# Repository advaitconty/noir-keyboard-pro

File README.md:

# Noir Keyboard Pro
A keyboard designed around the iPad Pro 11inch, mainly for use on the side

## Features
- Choc Red Pro switches that are hotswappable to your heart's content
- A simple design with extra pins if anything extra is required for a Pico
- A stabilizer-less design allowing for just nice uses

## BOM
*Prices in USD*

|Item                                                                                        |Quantity|Full Price|Remarks                  |Link                                                                                                                                                                                                                                                                                                                                                                                                                                                                                                                                                                                                                                                                                                                                                                                                                                                                                                                                                                                                                                                                                                                  |
|--------------------------------------------------------------------------------------------|--------|----------|-------------------------|----------------------------------------------------------------------------------------------------------------------------------------------------------------------------------------------------------------------------------------------------------------------------------------------------------------------------------------------------------------------------------------------------------------------------------------------------------------------------------------------------------------------------------------------------------------------------------------------------------------------------------------------------------------------------------------------------------------------------------------------------------------------------------------------------------------------------------------------------------------------------------------------------------------------------------------------------------------------------------------------------------------------------------------------------------------------------------------------------------------------|
|EVA foam                                                                                    |1       |$1.29     |Black variant 3mm 30x50  |https://www.lazada.sg/products/eva-foam-board-production-1-10mm-thick-foam-board-i2849696182-s19642596230.html?                                                                                                                                                                                                                                                                                                                                                                                                                                                                                                                                                                                                                                                                                                                                                                                                                                                                                                                                                                                                       |
|Rasperry Pi Pico H                                                                          |1       |$15.52    |                         |https://www.lazada.sg/products/original-raspberry-pi-pico-2-pico-with-wireless-wifi-development-boardpico-or-pico-h-with-pin-header-support-mciropythonc-i3197404377-s21712146500.html?                                                                                                                                                                                                                                                                                                                                                                                                                                                                                                                                                                                                                                                                                                                                                                                                                                                                                                                               |
|Micro-USB to USB-C cable                                                                    |1       |$3.87     |                         |https://www.lazada.sg/products/pdp-i1856449135-s9890909408.html?c=&channelLpJumpArgs=&clickTrackInfo=query%253Amicro%252Busb%252Bto%252Btype%252Bc%253Bnid%253A1856449135%253Bsrc%253ALazadaMainSrp%253Brn%253A82dbcd556e292181194f71b02f7c3592%253Bregion%253Asg%253Bsku%253A1856449135_SGAMZ%253Bprice%253A4.99%253Bclient%253Adesktop%253Bsupplier_id%253A1000061401%253Bbiz_source%253Ah5_internal%253Bslot%253A15%253Butlog_bucket_id%253A470687%253Basc_category_id%253A9537%253Bitem_id%253A1856449135%253Bsku_id%253A9890909408%253Bshop_id%253A152117%253BtemplateInfo%253A-1_A3_C%25231103_L%2523107878_E%2523&freeshipping=1&fs_ab=2&fuse_fs=&lang=en&location=China&price=4.99&priceCompare=skuId%3A9890909408%3Bsource%3Alazada-search-voucher%3Bsn%3A82dbcd556e292181194f71b02f7c3592%3BoriginPrice%3A499%3BdisplayPrice%3A499%3BsinglePromotionId%3A-1%3BsingleToolCode%3AmockedSalePrice%3BvoucherPricePlugin%3A0%3Btimestamp%3A1754101450229&ratingscore=4.95945945945946&request_id=82dbcd556e292181194f71b02f7c3592&review=308&sale=896&search=1&source=search&spm=a2o42.searchlist.list.15&stock=1|
|Kailh Choc Red Pro Switches (v1)                                                            |100     |$41.15    |x90 piece                |https://www.lazada.sg/products/kailh-low-profile-choc-switch-1350-rgb-for-keyboard-crystal-red-pro-pale-blue-pink-robin-silver-brown-white-yellow-orange-i3235755317-s21882496922.html?                                                                                                                                                                                                                                                                                                                                                                                                                                                                                                                                                                                                                                                                                                                                                                                                                                                                                                                               |
|Schotky Diodes                                                                              |100     |$4.58     |x100 piece               |https://www.lazada.sg/products/1n4148-do-35-small-signal-fast-switching-diode-i2668535659-s17380791247.html?                                                                                                                                                                                                                                                                                                                                                                                                                                                                                                                                                                                                                                                                                                                                                                                                                                                                                                                                                                                                          |
|Kailh Choc Hotswap Socket                                                                   |100     |$13.97    |x90 piece                |https://www.lazada.sg/products/kailh-hot-swap-plug-socket-for-kailh-low-profile-switch-choc-1350-i3216869960-s21821088673.html?                                                                                                                                                                                                                                                                                                                                                                                                                                                                                                                                                                                                                                                                                                                                                                                                                                                                                                                                                                                       |
|Noir Keyboard Pro PCB from JLCPCB                                                           |5       |$15.70    |Purchased                |NA                                                                                                                                                                                                                                                                                                                                                                                                                                                                                                                                                                                                                                                                                                                                                                                                                                                                                                                                                                                                                                                                                                                    |
|128x32 OLED Screen                                                                          |1       |$0.64     |White variant            |https://www.lazada.sg/products/pdp-i3161600227-s21505742950.html?c=&channelLpJumpArgs=&clickTrackInfo=query%253A128x32%252Boled%253Bnid%253A3161600227%253Bsrc%253ALazadaMainSrp%253Brn%253A38595f117eee84b7634c277fce23234a%253Bregion%253Asg%253Bsku%253A3161600227_SGAMZ%253Bprice%253A0.83%253Bclient%253Adesktop%253Bsupplier_id%253A1143054051%253Bbiz_source%253Ah5_internal%253Bslot%253A2%253Butlog_bucket_id%253A470687%253Basc_category_id%253A10000489%253Bitem_id%253A3161600227%253Bsku_id%253A21505742950%253Bshop_id%253A1260616%253BtemplateInfo%253A-1_A3_C%25231103_L%2523107878_E%2523&freeshipping=1&fs_ab=2&fuse_fs=&lang=en&location=China&price=0.83&priceCompare=skuId%3A21505742950%3Bsource%3Alazada-search-voucher%3Bsn%3A38595f117eee84b7634c277fce23234a%3BoriginPrice%3A83%3BdisplayPrice%3A83%3BsinglePromotionId%3A-1%3BsingleToolCode%3AmockedSalePrice%3BvoucherPricePlugin%3A0%3Btimestamp%3A1754102022697&ratingscore=5.0&request_id=38595f117eee84b7634c277fce23234a&review=1&sale=12&search=1&source=search&spm=a2o42.searchlist.list.2&stock=1                                |
|Shipping label                                                                              |1       |$2.87     |For 3D printed parts     |https://www.singpost.com/send-receive/sending-within-singapore/postage-paid-packaging/smartpac                                                                                                                                                                                                                                                                                                                                                                                                                                                                                                                                                                                                                                                                                                                                                                                                                                                                                                                                                                                                                        |
|Chisel tip for pinecil (my pinecil tip doesn't work - tried everything including steel wool)|1       |$8.58     |For my broken pinecil tip + getting D24 variant|https://www.lazada.sg/products/pine64-ts100-ts101-soldering-iron-tips-replacement-various-models-of-pinecil-v2-electric-soldering-iron-tip-ts-series-bc2-ils-k-i3477953576-s23017502165.html?                                                                                                                                                                                                                                                                                                                                                                                                                                                                                                                                                                                                                                                                                                                                                                                                                                                                                                                         |
|Female headers for pico + display                                                           |2       |$1.46     |1x 20 pin + 1x 4 pin     |https://www.lazada.sg//products/i2845738229-s19616005484.html?spm=a2o42.cart.0.0.732e7a93AmAcCy&urlFlag=true                                                                                                                                                                                                                                                                                                                                                                                                                                                                                                                                                                                                                                                                                                                                                                                                                                                                                                                                                                                                          |
|Shipping Fees for everything                                                                |1       |$15       |                         |NA                                                                                                                                                                                                                                                                                                                                                                                                                                                                                                                                                                                                                                                                                                                                                                                                                                                                                                                                                                                                                                                                                                                    |

*Total: USD123.17 (SGD158.59)*

## Photos in CAD

*PCB*

*KiCad Schematic*

*Case design*

*Keycaps*

Full design of everything
---

## Credits
Massive kudos to @joe-scotto's ScottoKeebs repo (KiCad Footprints from the "Extras" folder, keyswitch design roughly taken from him)
Shapr3D and KiCad for their wonderful software

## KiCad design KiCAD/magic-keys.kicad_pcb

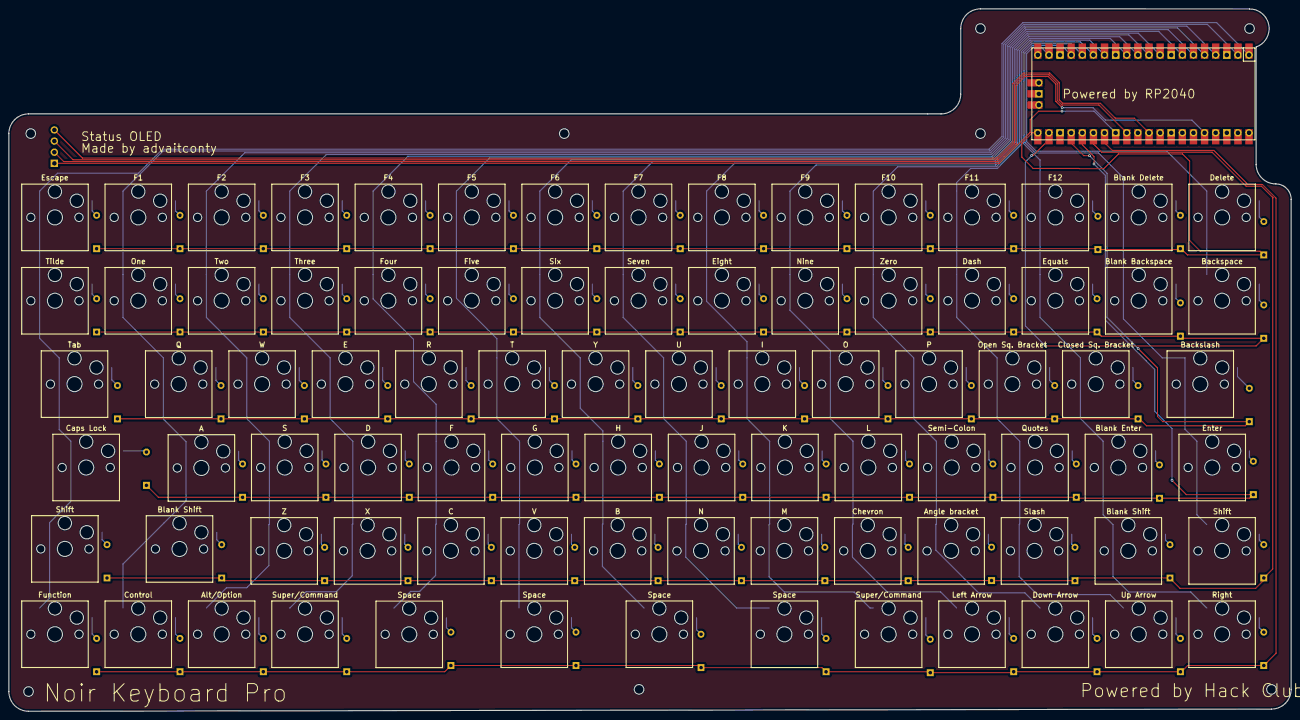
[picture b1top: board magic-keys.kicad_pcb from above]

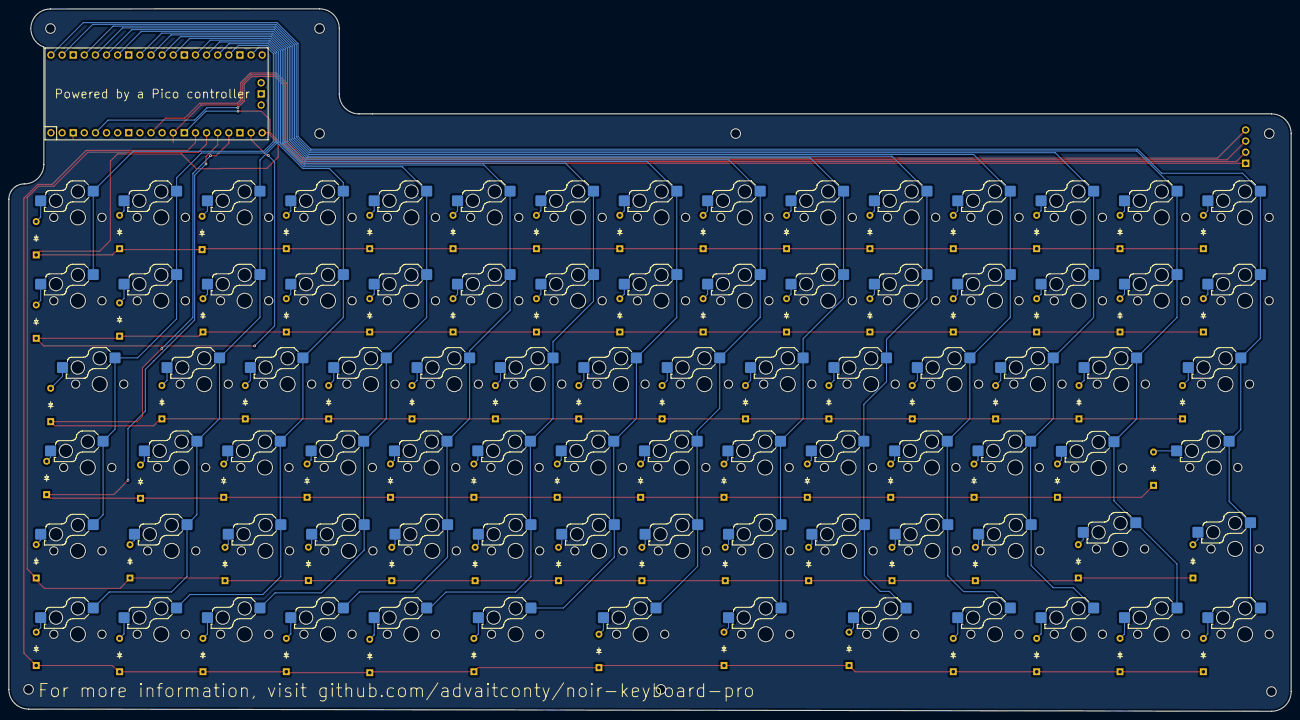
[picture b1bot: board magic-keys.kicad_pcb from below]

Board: 2 copper layers, 293.0 x 160.5 mm, 172 parts (85 on the bottom side), 110 nets.

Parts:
0)Diode1, 1!Diode1, 2@Diode1, 3#Diode1, 4$Diode1, 5%Diode1, 6^Diode1, 7&Diode1, 8*Diode1, 9(Diode1: Diode; Diode_DO-35
'"Diode1: Diode; Diode_DO-35
-_Diode1: Diode; Diode_DO-35
/?Diode1: Diode; Diode_DO-35
;:Diode1: Diode; Diode_DO-35
<,Diode1: Diode; Diode_DO-35
=+Diode1: Diode; Diode_DO-35
>.Diode1: Diode; Diode_DO-35
A: Keyswitch; Hotswap_Choc_V1_1.00u
ADiode1: Diode; Diode_DO-35
Alt/Option: Keyswitch; Hotswap_Choc_V1_1.00u
Angle bracket: Keyswitch; Hotswap_Choc_V1_1.00u
B: Keyswitch; Hotswap_Choc_V1_1.00u
BDiode1: Diode; Diode_DO-35
Backslash: Keyswitch; Hotswap_Choc_V1_1.50u
Backspace: Keyswitch; Hotswap_Choc_V1_1.00u
BackspaceDiode1, BackspaceDiode2: Diode; Diode_DO-35
Blank Backspace: Keyswitch; Hotswap_Choc_V1_1.00u
Blank Delete: Keyswitch; Hotswap_Choc_V1_1.00u
Blank Enter: Keyswitch; Hotswap_Choc_V1_1.00u
Blank Shift: Keyswitch; Hotswap_Choc_V1_1.25u
Blank Shift#2: Keyswitch; Hotswap_Choc_V1_1.50u
C: Keyswitch; Hotswap_Choc_V1_1.00u
CDiode1: Diode; Diode_DO-35
Caps Lock: Keyswitch; Hotswap_Choc_V1_1.75u
CapsLockDiode1: Diode; Diode_DO-35
Chevron: Keyswitch; Hotswap_Choc_V1_1.00u
Closed Sq. Bracket: Keyswitch; Hotswap_Choc_V1_1.00u
CmdDiode1, CmdDiode2: Diode; Diode_DO-35
Control: Keyswitch; Hotswap_Choc_V1_1.00u
ControlDiode1: Diode; Diode_DO-35
D: Keyswitch; Hotswap_Choc_V1_1.00u
DDiode1: Diode; Diode_DO-35
Dash: Keyswitch; Hotswap_Choc_V1_1.00u
DelDiode1, DelDiode2: Diode; Diode_DO-35
Delete: Keyswitch; Hotswap_Choc_V1_1.00u
Down Arrow: Keyswitch; Hotswap_Choc_V1_1.00u
DownDiode1: Diode; Diode_DO-35
E: Keyswitch; Hotswap_Choc_V1_1.00u
EDiode1: Diode; Diode_DO-35
Eight: Keyswitch; Hotswap_Choc_V1_1.00u
Enter: Keyswitch; Hotswap_Choc_V1_1.25u
EnterDiode1, EnterDiode2: Diode; Diode_DO-35
Equals: Keyswitch; Hotswap_Choc_V1_1.00u
EscDiode1: Diode; Diode_DO-35
Escape: Keyswitch; Hotswap_Choc_V1_1.00u
F, F1, F2, F3, F4, F5, F6, F7, F8, F9, F10, F11, F12: Keyswitch; Hotswap_Choc_V1_1.00u
F1Diode1, F2Diode1, F3Diode1, F4Diode1, F5Diode1, F6Diode1, F7Diode1, F8Diode1, F9Diode1, F10Diode1, F11Diode1, F12Diode1: Diode; Diode_DO-35
FDiode1: Diode; Diode_DO-35
Five: Keyswitch; Hotswap_Choc_V1_1.00u
FnDiode1: Diode; Diode_DO-35
Four: Keyswitch; Hotswap_Choc_V1_1.00u
Function: Keyswitch; Hotswap_Choc_V1_1.00u
G: Keyswitch; Hotswap_Choc_V1_1.00u
GDiode1: Diode; Diode_DO-35
H: Keyswitch; Hotswap_Choc_V1_1.00u
HDiode1: Diode; Diode_DO-35
I: Keyswitch; Hotswap_Choc_V1_1.00u
IDiode1: Diode; Diode_DO-35
J: Keyswitch; Hotswap_Choc_V1_1.00u
J2: OLED_128x32
JDiode1: Diode; Diode_DO-35
K: Keyswitch; Hotswap_Choc_V1_1.00u
KDiode1: Diode; Diode_DO-35
L: Keyswitch; Hotswap_Choc_V1_1.00u
LDiode1: Diode; Diode_DO-35
Left Arrow: Keyswitch; Hotswap_Choc_V1_1.00u
LeftDiode1: Diode; Diode_DO-35
M: Keyswitch; Hotswap_Choc_V1_1.00u
MDiode1: Diode; Diode_DO-35
N: Keyswitch; Hotswap_Choc_V1_1.00u
NDiode1: Diode; Diode_DO-35
Nine: Keyswitch; Hotswap_Choc_V1_1.00u
O: Keyswitch; Hotswap_Choc_V1_1.00u
ODiode1: Diode; Diode_DO-35
One: Keyswitch; Hotswap_Choc_V1_1.00u
Open Sq. Bracket: Keyswitch; Hotswap_Choc_V1_1.00u
OptionDiode1: Diode; Diode_DO-35
P: Keyswitch; Hotswap_Choc_V1_1.00u
PDiode1: Diode; Diode_DO-35
Q: Keyswitch; Hotswap_Choc_V1_1.00u
QDiode1: Diode; Diode_DO-35
Quotes: Keyswitch; Hotswap_Choc_V1_1.00u
R: Keyswitch; Hotswap_Choc_V1_1.00u
RDiode1: Diode; Diode_DO-35
Right: Keyswitch; Hotswap_Choc_V1_1.00u
RightDiode1: Diode; Diode_DO-35
S: Keyswitch; Hotswap_Choc_V1_1.00u
SDiode1: Diode; Diode_DO-35
Semi-Colon: Keyswitch; Hotswap_Choc_V1_1.00u
Seven: Keyswitch; Hotswap_Choc_V1_1.00u
Shift: Keyswitch; Hotswap_Choc_V1_1.25u
Shift#2: Keyswitch; Hotswap_Choc_V1_1.00u
ShiftDiode1, ShiftDiode2, ShiftDiode3, ShiftDiode4: Diode; Diode_DO-35
Six: Keyswitch; Hotswap_Choc_V1_1.00u
Slash: Keyswitch; Hotswap_Choc_V1_1.00u
Space: Keyswitch; Hotswap_Choc_V1_1.50u
Space#2, Space#3, Space#4: Keyswitch; Hotswap_Choc_V1_1.50u
SpaceDiode1, SpaceDiode2, SpaceDiode3, SpaceDiode4: Diode; Diode_DO-35
Super/Command: Keyswitch; Hotswap_Choc_V1_1.00u
Super/Command#2: Keyswitch; Hotswap_Choc_V1_1.00u
T: Keyswitch; Hotswap_Choc_V1_1.00u
TDiode1: Diode; Diode_DO-35
Tab: Keyswitch; Hotswap_Choc_V1_1.50u
TabDiode1: Diode; Diode_DO-35
Three: Keyswitch; Hotswap_Choc_V1_1.00u
Tilde: Keyswitch; Hotswap_Choc_V1_1.00u
Two: Keyswitch; Hotswap_Choc_V1_1.00u
U: Keyswitch; Hotswap_Choc_V1_1.00u
U1: Raspberry_Pi_Pico
UDiode1: Diode; Diode_DO-35
Up Arrow: Keyswitch; Hotswap_Choc_V1_1.00u
UpDiode1: Diode; Diode_DO-35
V: Keyswitch; Hotswap_Choc_V1_1.00u
VDiode1: Diode; Diode_DO-35
W: Keyswitch; Hotswap_Choc_V1_1.00u
WDiode1: Diode; Diode_DO-35
X: Keyswitch; Hotswap_Choc_V1_1.00u
XDiode1: Diode; Diode_DO-35
Y: Keyswitch; Hotswap_Choc_V1_1.00u
YDiode1: Diode; Diode_DO-35
Z: Keyswitch; Hotswap_Choc_V1_1.00u
ZDiode1: Diode; Diode_DO-35
Zero: Keyswitch; Hotswap_Choc_V1_1.00u
[{Diode1: Diode; Diode_DO-35
\|Diode1: Diode; Diode_DO-35
]}Diode1: Diode; Diode_DO-35
`~Diode1: Diode; Diode_DO-35

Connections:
Column 0: Caps Lock.1, Escape.1, Function.1, Shift.1, Tab.1, Tilde.1, U1.1 (GPIO0)
Column 1: A.1, Blank Shift#2.1, Control.1, F1.1, One.1, Q.1, U1.2 (GPIO1)
Column 2: Alt/Option.1, F2.1, S.1, Two.1, U1.4 (GPIO2), W.1, Z.1
Column 3: D.1, E.1, F3.1, Super/Command.1, Three.1, U1.5 (GPIO3), X.1
Column 4: C.1, F.1, F4.1, Four.1, R.1, Space#3.1, U1.6 (GPIO4)
Column 5: F5.1, Five.1, G.1, Space#4.1, T.1, U1.7 (GPIO5), V.1
Column 6: B.1, F6.1, H.1, Six.1, Space.1, U1.9 (GPIO6), Y.1
Column 7: F7.1, J.1, N.1, Seven.1, Space#2.1, U.1, U1.10 (GPIO7)
Column 8: Eight.1, F8.1, I.1, K.1, M.1, Super/Command#2.1, U1.11 (GPIO8)
Column 9: Chevron.1, F9.1, L.1, Left Arrow.1, Nine.1, O.1, U1.12 (GPIO9)
Column 10: Angle bracket.1, Down Arrow.1, F10.1, P.1, Semi-Colon.1, U1.14 (GPIO10), Zero.1
Column 11: Dash.1, F11.1, Open Sq. Bracket.1, Quotes.1, Slash.1, U1.15 (GPIO11), Up Arrow.1
Column 12: Blank Enter.1, Blank Shift.1, Closed Sq. Bracket.1, Equals.1, F12.1, Right.1, U1.16 (GPIO12)
Column 13: Backslash.1, Blank Backspace.1, Blank Delete.1, Enter.1, Shift#2.1, U1.17 (GPIO13)
Column 14: Backspace.1, Delete.1, U1.19 (GPIO14)
unnamed: 0)Diode1.2 (A), Zero.2
unnamed: 1!Diode1.2 (A), One.2
unnamed: 2@Diode1.2 (A), Two.2
unnamed: 3#Diode1.2 (A), Three.2
unnamed: 4$Diode1.2 (A), Four.2
unnamed: 5%Diode1.2 (A), Five.2
unnamed: 6^Diode1.2 (A), Six.2
unnamed: 7&Diode1.2 (A), Seven.2
unnamed: 8*Diode1.2 (A), Eight.2
unnamed: 9(Diode1.2 (A), Nine.2
unnamed: '"Diode1.2 (A), Quotes.2
unnamed: -_Diode1.2 (A), Dash.2
unnamed: /?Diode1.2 (A), Slash.2
unnamed: ;:Diode1.2 (A), Semi-Colon.2
unnamed: <,Diode1.2 (A), Chevron.2
unnamed: =+Diode1.2 (A), Equals.2
unnamed: >.Diode1.2 (A), Angle bracket.2
unnamed: A.2, ADiode1.2 (A)
unnamed: B.2, BDiode1.2 (A)
unnamed: BackspaceDiode1.2 (A), Blank Backspace.2
unnamed: Backspace.2, BackspaceDiode2.2 (A)
unnamed: C.2, CDiode1.2 (A)
unnamed: Caps Lock.2, CapsLockDiode1.2 (A)
unnamed: CmdDiode1.2 (A), Super/Command.2
unnamed: CmdDiode2.2 (A), Super/Command#2.2
unnamed: Control.2, ControlDiode1.2 (A)
unnamed: D.2, DDiode1.2 (A)
unnamed: Blank Delete.2, DelDiode1.2 (A)
unnamed: DelDiode2.2 (A), Delete.2
unnamed: Down Arrow.2, DownDiode1.2 (A)
unnamed: E.2, EDiode1.2 (A)
unnamed: Blank Enter.2, EnterDiode1.2 (A)
unnamed: Enter.2, EnterDiode2.2 (A)
unnamed: EscDiode1.2 (A), Escape.2
unnamed: F1.2, F1Diode1.2 (A)
unnamed: F2.2, F2Diode1.2 (A)
unnamed: F3.2, F3Diode1.2 (A)
unnamed: F4.2, F4Diode1.2 (A)
unnamed: F5.2, F5Diode1.2 (A)
unnamed: F6.2, F6Diode1.2 (A)
unnamed: F7.2, F7Diode1.2 (A)
unnamed: F8.2, F8Diode1.2 (A)
unnamed: F9.2, F9Diode1.2 (A)
unnamed: F10.2, F10Diode1.2 (A)
unnamed: F11.2, F11Diode1.2 (A)
unnamed: F12.2, F12Diode1.2 (A)
unnamed: F.2, FDiode1.2 (A)
unnamed: FnDiode1.2 (A), Function.2
unnamed: G.2, GDiode1.2 (A)
unnamed: H.2, HDiode1.2 (A)
unnamed: I.2, IDiode1.2 (A)
unnamed: J2.1 (GND), U1.28 (GND)
unnamed: J2.3 (SCL), U1.29 (GPIO22)
unnamed: J2.4 (SDA), U1.31 (GPIO26_ADC0)
unnamed: J2.2 (VCC), U1.36 (3V3)
unnamed: J.2, JDiode1.2 (A)
unnamed: K.2, KDiode1.2 (A)
unnamed: L.2, LDiode1.2 (A)
unnamed: Left Arrow.2, LeftDiode1.2 (A)
unnamed: M.2, MDiode1.2 (A)
unnamed: N.2, NDiode1.2 (A)
unnamed: O.2, ODiode1.2 (A)
unnamed: Alt/Option.2, OptionDiode1.2 (A)
unnamed: P.2, PDiode1.2 (A)
unnamed: Q.2, QDiode1.2 (A)
unnamed: R.2, RDiode1.2 (A)
unnamed: Right.2, RightDiode1.2 (A)
unnamed: S.2, SDiode1.2 (A)
unnamed: Shift.2, ShiftDiode1.2 (A)
unnamed: Blank Shift.2, ShiftDiode2.2 (A)
unnamed: Blank Shift#2.2, ShiftDiode3.2 (A)
unnamed: Shift#2.2, ShiftDiode4.2 (A)
unnamed: Space#3.2, SpaceDiode1.2 (A)
unnamed: Space#4.2, SpaceDiode2.2 (A)
unnamed: Space.2, SpaceDiode3.2 (A)
unnamed: Space#2.2, SpaceDiode4.2 (A)
unnamed: T.2, TDiode1.2 (A)
unnamed: Tab.2, TabDiode1.2 (A)
unnamed: U.2, UDiode1.2 (A)
unnamed: Up Arrow.2, UpDiode1.2 (A)
unnamed: V.2, VDiode1.2 (A)
unnamed: W.2, WDiode1.2 (A)
unnamed: X.2, XDiode1.2 (A)
unnamed: Y.2, YDiode1.2 (A)
unnamed: Z.2, ZDiode1.2 (A)
unnamed: Open Sq. Bracket.2, [{Diode1.2 (A)
unnamed: Backslash.2, \|Diode1.2 (A)
unnamed: Closed Sq. Bracket.2, ]}Diode1.2 (A)
unnamed: Tilde.2, `~Diode1.2 (A)
Row 0: DelDiode1.1 (K), DelDiode2.1 (K), EscDiode1.1 (K), F1Diode1.1 (K), F2Diode1.1 (K), F3Diode1.1 (K), F4Diode1.1 (K), F5Diode1.1 (K), F6Diode1.1 (K), F7Diode1.1 (K), F8Diode1.1 (K), F9Diode1.1 (K), F10Diode1.1 (K), F11Diode1.1 (K), F12Diode1.1 (K), U1.21 (GPIO16)
Row 1: 0)Diode1.1 (K), 1!Diode1.1 (K), 2@Diode1.1 (K), 3#Diode1.1 (K), 4$Diode1.1 (K), 5%Diode1.1 (K), 6^Diode1.1 (K), 7&Diode1.1 (K), 8*Diode1.1 (K), 9(Diode1.1 (K), -_Diode1.1 (K), =+Diode1.1 (K), BackspaceDiode1.1 (K), BackspaceDiode2.1 (K), U1.22 (GPIO17), `~Diode1.1 (K)
Row 2: EDiode1.1 (K), IDiode1.1 (K), ODiode1.1 (K), PDiode1.1 (K), QDiode1.1 (K), RDiode1.1 (K), TDiode1.1 (K), TabDiode1.1 (K), U1.24 (GPIO18), UDiode1.1 (K), WDiode1.1 (K), YDiode1.1 (K), [{Diode1.1 (K), \|Diode1.1 (K), ]}Diode1.1 (K)
Row 3: '"Diode1.1 (K), ;:Diode1.1 (K), ADiode1.1 (K), CapsLockDiode1.1 (K), DDiode1.1 (K), EnterDiode1.1 (K), EnterDiode2.1 (K), FDiode1.1 (K), GDiode1.1 (K), HDiode1.1 (K), JDiode1.1 (K), KDiode1.1 (K), LDiode1.1 (K), SDiode1.1 (K), U1.25 (GPIO19)
Row 4: /?Diode1.1 (K), <,Diode1.1 (K), >.Diode1.1 (K), BDiode1.1 (K), CDiode1.1 (K), MDiode1.1 (K), NDiode1.1 (K), ShiftDiode1.1 (K), ShiftDiode2.1 (K), ShiftDiode3.1 (K), ShiftDiode4.1 (K), U1.26 (GPIO20), VDiode1.1 (K), XDiode1.1 (K), ZDiode1.1 (K)
Row 5: CmdDiode1.1 (K), CmdDiode2.1 (K), ControlDiode1.1 (K), DownDiode1.1 (K), FnDiode1.1 (K), LeftDiode1.1 (K), OptionDiode1.1 (K), RightDiode1.1 (K), SpaceDiode1.1 (K), SpaceDiode2.1 (K), SpaceDiode3.1 (K), SpaceDiode4.1 (K), U1.27 (GPIO21), UpDiode1.1 (K)

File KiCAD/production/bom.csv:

Designator,Footprint,Quantity,Value,LCSC Part #
"'""DIODE1, -_DIODE1, /?DIODE1, 0)DIODE1, 1!DIODE1, 2@DIODE1, 3#DIODE1, 4$DIODE1, 5%DIODE1, 6^DIODE1, 7&DIODE1, 8*DIODE1, 9(DIODE1, ;:DIODE1, <,DIODE1, =+DIODE1, >.DIODE1, ADIODE1, BACKSPACEDIODE1, BACKSPACEDIODE2, BDIODE1, CAPSLOCKDIODE1, CDIODE1, CMDDIODE1, CMDDIODE2, CONTROLDIODE1, DDIODE1, DELDIODE1, DELDIODE2, DOWNDIODE1, EDIODE1, ENTERDIODE1, ENTERDIODE2, ESCDIODE1, F10DIODE1, F11DIODE1, F12DIODE1, F1DIODE1, F2DIODE1, F3DIODE1, F4DIODE1, F5DIODE1, F6DIODE1, F7DIODE1, F8DIODE1, F9DIODE1, FDIODE1, FNDIODE1, GDIODE1, HDIODE1, IDIODE1, JDIODE1, KDIODE1, LDIODE1, LEFTDIODE1, MDIODE1, NDIODE1, ODIODE1, OPTIONDIODE1, PDIODE1, QDIODE1, RDIODE1, RIGHTDIODE1, SDIODE1, SHIFTDIODE1, SHIFTDIODE2, SHIFTDIODE3, SHIFTDIODE4, SPACEDIODE1, SPACEDIODE2, SPACEDIODE3, SPACEDIODE4, TABDIODE1, TDIODE1, UDIODE1, UPDIODE1, VDIODE1, WDIODE1, XDIODE1, YDIODE1, ZDIODE1, [{DIODE1, \|DIODE1, ]}DIODE1, `~DIODE1",Diode_DO-35,85,Diode,
"A, ALT/OPTION, ANGLE BRACKET, B, BACKSPACE, BLANK BACKSPACE, BLANK DELETE, BLANK ENTER, C, CHEVRON, CLOSED SQ. BRACKET, CONTROL, D, DASH, DELETE, DOWN ARROW, E, EIGHT, EQUALS, ESCAPE, F, F1, F10, F11, F12, F2, F3, F4, F5, F6, F7, F8, F9, FIVE, FOUR, FUNCTION, G, H, I, J, K, L, LEFT ARROW, M, N, NINE, O, ONE, OPEN SQ. BRACKET, P, Q, QUOTES, R, RIGHT, S, SEMI-COLON, SEVEN, SHIFT, SIX, SLASH, SUPER/COMMAND_2, SUPER/COMMAND, T, THREE, TILDE, TWO, U, UP ARROW, V, W, X, Y, Z, ZERO",Hotswap_Choc_V1_1.00u,74,Keyswitch,
"BACKSLASH, BLANK SHIFT, SPACE_4, SPACE_3, SPACE_2, SPACE, TAB",Hotswap_Choc_V1_1.50u,7,Keyswitch,
"BLANK SHIFT_2, ENTER, SHIFT_2",Hotswap_Choc_V1_1.25u,3,Keyswitch,
CAPS LOCK,Hotswap_Choc_V1_1.75u,1,Keyswitch,
J2,OLED_128x32,1,OLED_128x32,
U1,Raspberry_Pi_Pico,1,Raspberry_Pi_Pico,

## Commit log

2025-06-06 added my first keyboard attempt! (didn't add the tutorial stuff tho)
2025-06-06 added journal, added readme, refactored files
2025-06-06 added more stuff for magickeys
2025-06-07 changed layout for stabs (to be keys), finished schematics
2025-06-08 Optimised wiring
2025-06-09 added mount pounts, added case
2025-06-09 changed shapr3d file to use LFS
2025-06-09 forgot to commit updated PCB
2025-06-09 edited journal
2025-06-09 updated readme and journal
2025-06-09 added keycaps design
2025-06-09 added LFS for the Shapr files
2025-06-11 Updated files
2025-06-11 Removed BOM
2025-06-12 added final files
2025-06-12 Updated keycaps
2025-06-12 Updated Journal, added firmware
2025-06-12 added finances
2025-06-13 added OLED screengit status
2025-06-13 modify finances
2025-06-20 added design of everything
2025-06-26 addded STEP for PCB case
2025-06-26 edited attributes
2025-07-04 added STEP CADs of full PCB
2025-07-04 Added BOM
2025-07-23 added LFS stuff
2025-07-24 edited for review
2025-07-30 added a stuff i missed out
2025-08-02 updated BOM, retraced PCB for a nicer thing
2025-08-02 added pinecil tip
2025-08-05 updated BOM, sending for final re-review after updating images
